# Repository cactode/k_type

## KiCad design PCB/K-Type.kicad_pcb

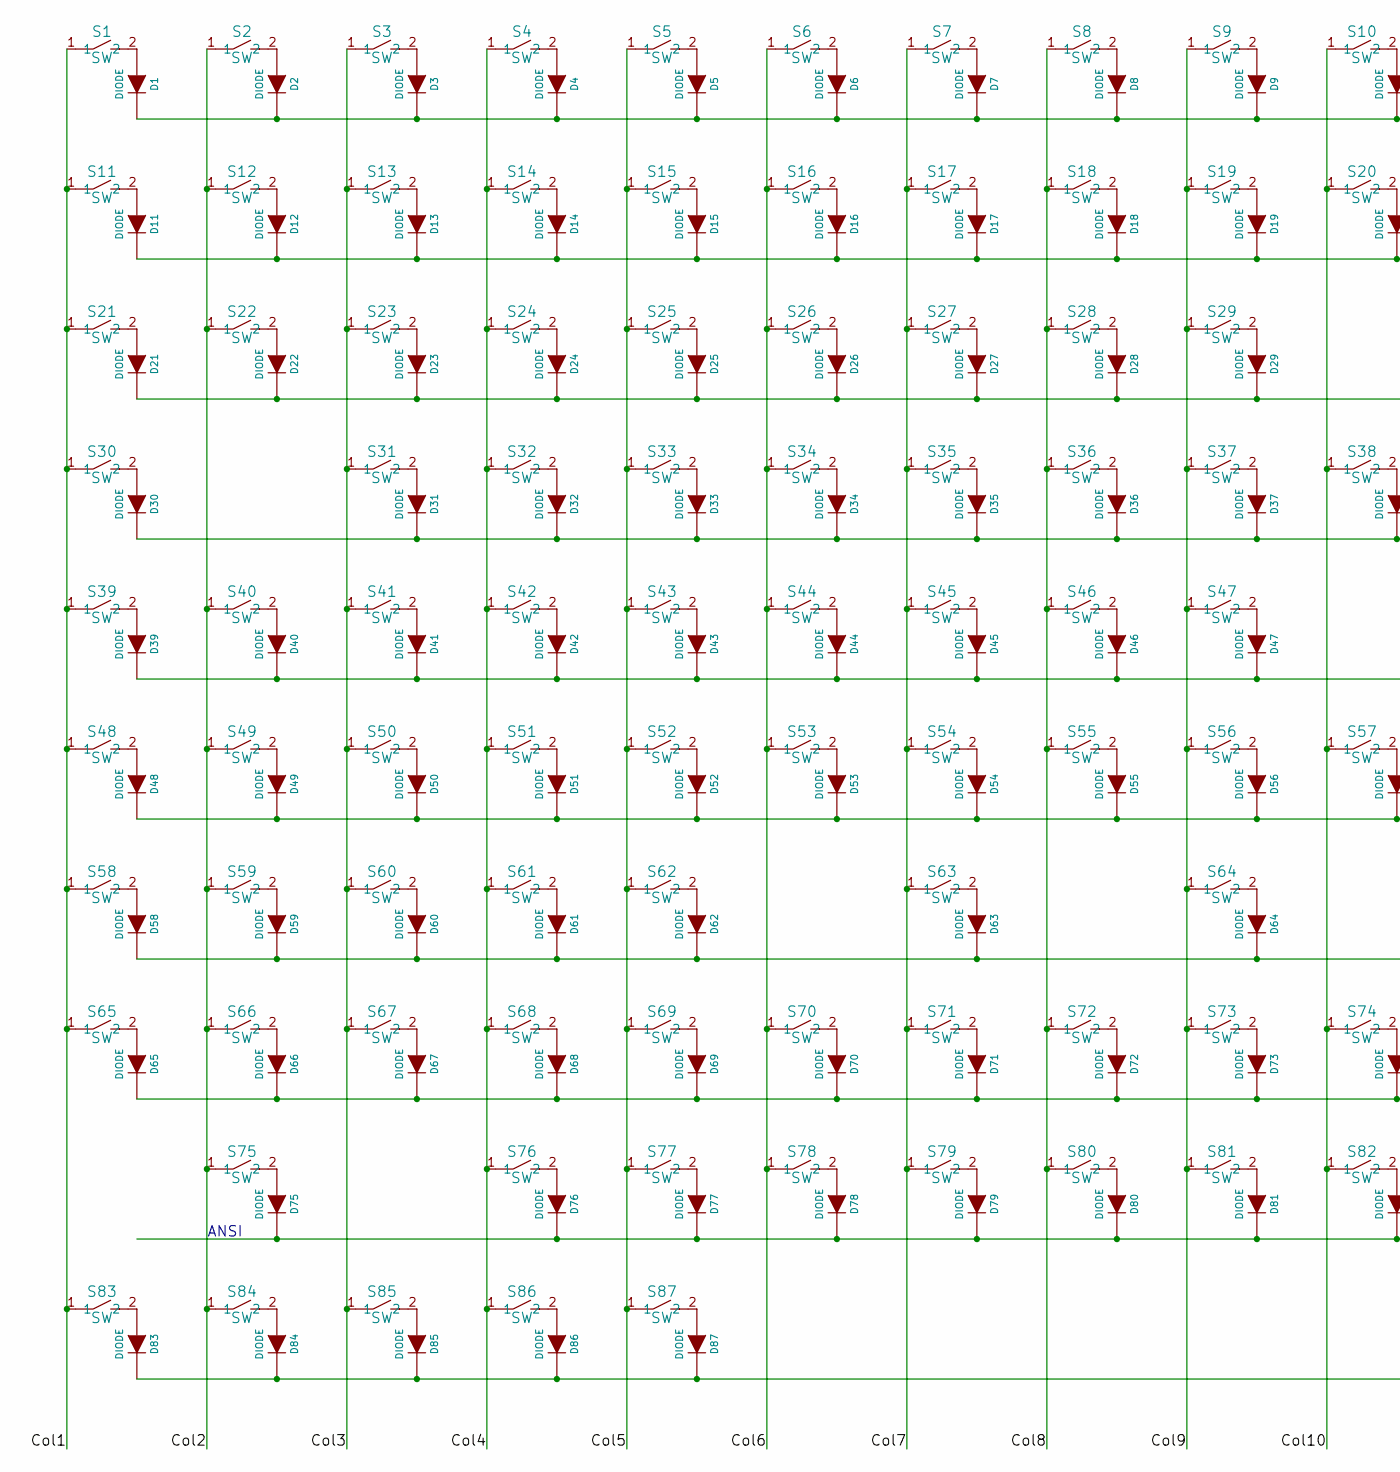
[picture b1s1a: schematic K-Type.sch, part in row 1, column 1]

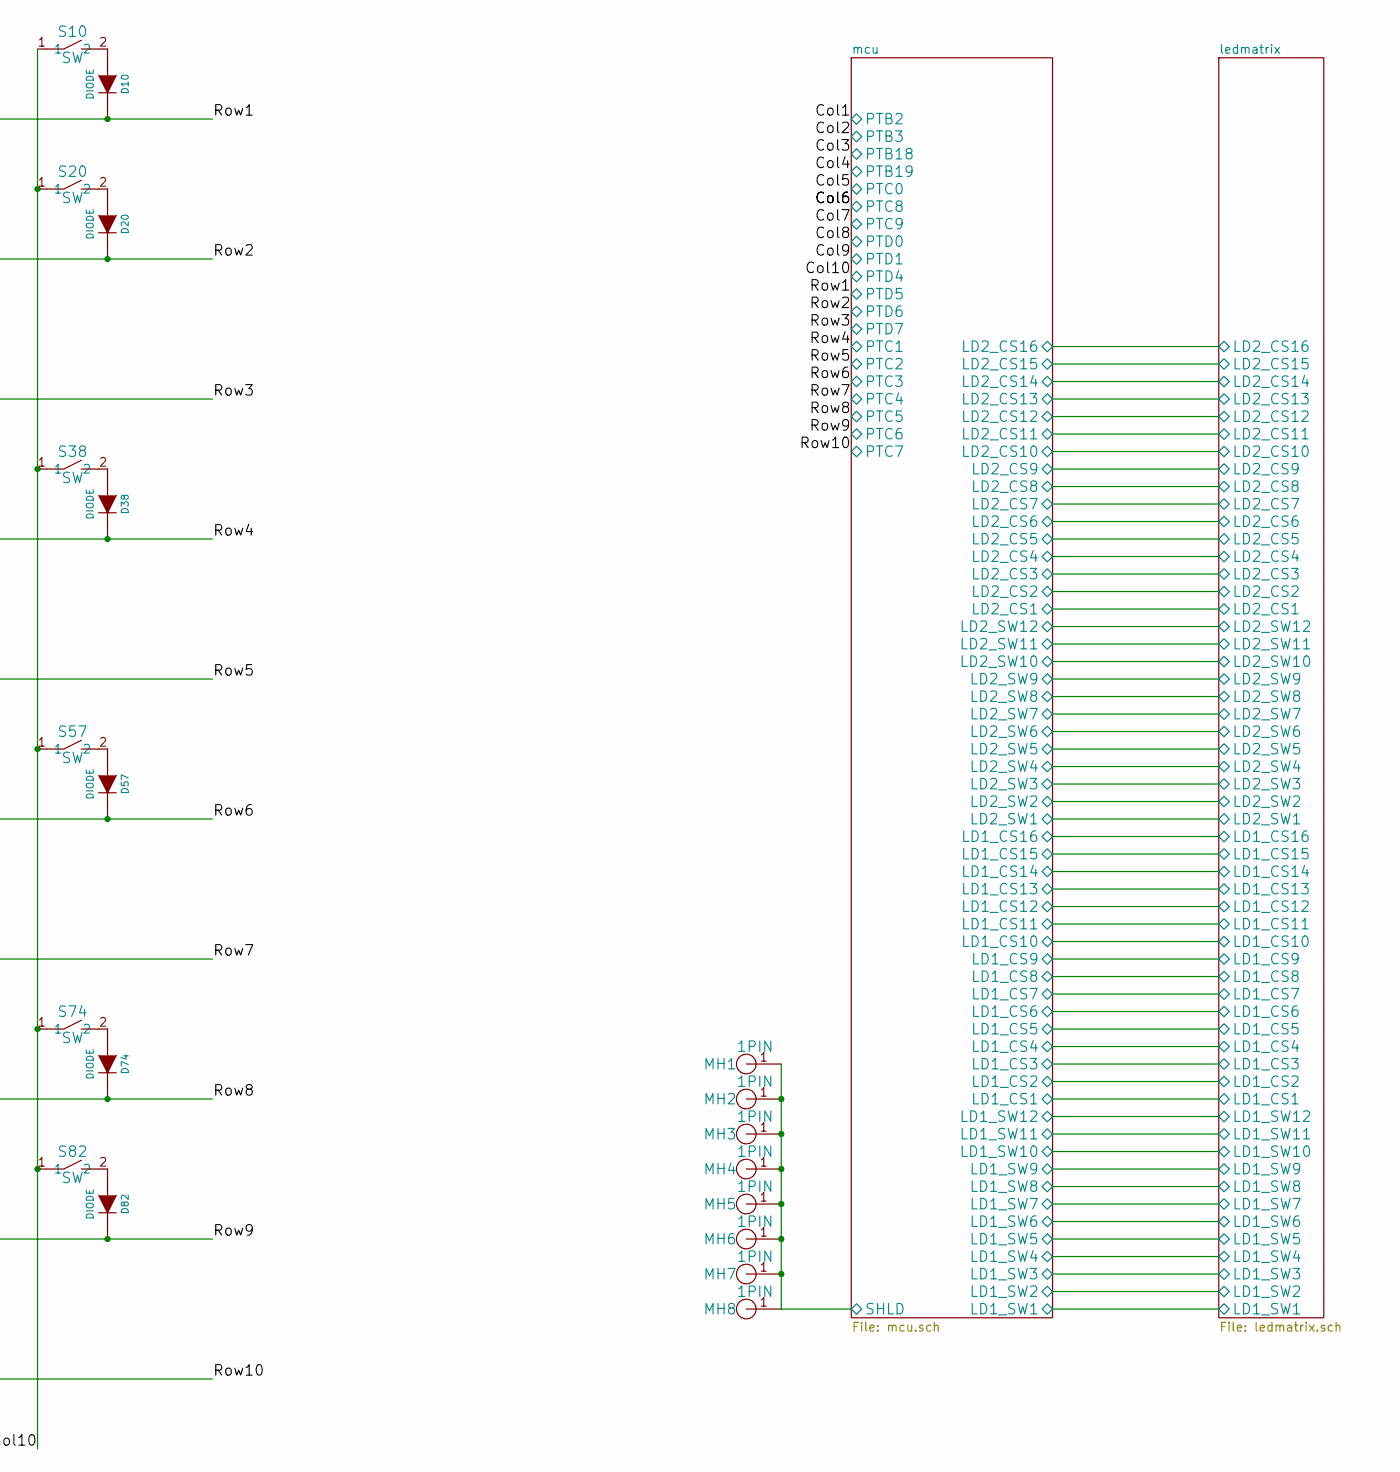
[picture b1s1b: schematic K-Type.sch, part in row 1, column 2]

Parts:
D1, D2, D3, D4, D5, D6, D7, D8, D9, D10, D11, D12, D13, D14, D15, D16, D17, D18, D19, D20, D21, D22, D23, D24, D25, D26, D27, D28, D29, D30, D31, D32, D33, D34, D35, D36, D37, D38, D39, D40, D41, D42, D43, D44, D45, D46, D47, D48, D49, D50, D51, D52, D53, D54, D55, D56, D57, D58, D59, D60, D61, D62, D63, D64, D65, D66, D67, D68, D69, D70, D71, D72, D73, D74, D75, D76, D77, D78, D79, D80, D81, D82, D83, D84, D85, D86, D87: DIODE; SOD-523
MH1, MH2, MH3, MH4, MH5, MH6, MH7, MH8: 1PIN; 1PAD
S1, S2, S3, S4, S5, S6, S7, S8, S9, S10, S11, S12, S13, S14, S15, S16, S17, S18, S19, S20, S21, S22, S23, S24, S25, S26, S27, S28, S29, S30, S31, S32, S33, S34, S35, S36, S37, S38, S39, S40, S41, S42, S43, S44, S45, S46, S47, S48, S49, S50, S51, S52, S53, S54, S55, S56, S57, S58, S59, S60, S61, S62, S63, S64, S65, S66, S67, S68, S69, S70, S71, S72, S73, S74, S75, S76, S77, S78, S79, S80, S81, S82, S83, S84, S85, S86, S87: SW; SW_SOCKET_COMBINED_T

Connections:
/Col1: S1.1, S11.1, S21.1, S30.1, S39.1, S48.1, S58.1, S65.1, S83.1; also elsewhere on the board
/Col2: S2.1, S12.1, S22.1, S40.1, S49.1, S59.1, S66.1, S75.1, S84.1; also elsewhere on the board
/Col3: S3.1, S13.1, S23.1, S31.1, S41.1, S50.1, S60.1, S67.1, S85.1; also elsewhere on the board
/Col4: S4.1, S14.1, S24.1, S32.1, S42.1, S51.1, S61.1, S68.1, S76.1, S86.1; also elsewhere on the board
/Col5: S5.1, S15.1, S25.1, S33.1, S43.1, S52.1, S62.1, S69.1, S77.1, S87.1; also elsewhere on the board
/Col6: S6.1, S16.1, S26.1, S34.1, S44.1, S53.1, S70.1, S78.1; also elsewhere on the board
/Col7: S7.1, S17.1, S27.1, S35.1, S45.1, S54.1, S63.1, S71.1, S79.1; also elsewhere on the board
/Col8: S8.1, S18.1, S28.1, S36.1, S46.1, S55.1, S72.1, S80.1; also elsewhere on the board
/Col9: S9.1, S19.1, S29.1, S37.1, S47.1, S56.1, S64.1, S73.1, S81.1; also elsewhere on the board
/Col10: S10.1, S20.1, S38.1, S57.1, S74.1, S82.1; also elsewhere on the board
/Row1: D1.2 (K), D2.2 (K), D3.2 (K), D4.2 (K), D5.2 (K), D6.2 (K), D7.2 (K), D8.2 (K), D9.2 (K), D10.2 (K); also elsewhere on the board
/Row2: D11.2 (K), D12.2 (K), D13.2 (K), D14.2 (K), D15.2 (K), D16.2 (K), D17.2 (K), D18.2 (K), D19.2 (K), D20.2 (K); also elsewhere on the board
/Row3: D21.2 (K), D22.2 (K), D23.2 (K), D24.2 (K), D25.2 (K), D26.2 (K), D27.2 (K), D28.2 (K), D29.2 (K); also elsewhere on the board
/Row4: D30.2 (K), D31.2 (K), D32.2 (K), D33.2 (K), D34.2 (K), D35.2 (K), D36.2 (K), D37.2 (K), D38.2 (K); also elsewhere on the board
/Row5: D39.2 (K), D40.2 (K), D41.2 (K), D42.2 (K), D43.2 (K), D44.2 (K), D45.2 (K), D46.2 (K), D47.2 (K); also elsewhere on the board
/Row6: D48.2 (K), D49.2 (K), D50.2 (K), D51.2 (K), D52.2 (K), D53.2 (K), D54.2 (K), D55.2 (K), D56.2 (K), D57.2 (K); also elsewhere on the board
/Row7: D58.2 (K), D59.2 (K), D60.2 (K), D61.2 (K), D62.2 (K), D63.2 (K), D64.2 (K); also elsewhere on the board
/Row8: D65.2 (K), D66.2 (K), D67.2 (K), D68.2 (K), D69.2 (K), D70.2 (K), D71.2 (K), D72.2 (K), D73.2 (K), D74.2 (K); also elsewhere on the board
/Row9: D75.2 (K), D76.2 (K), D77.2 (K), D78.2 (K), D79.2 (K), D80.2 (K), D81.2 (K), D82.2 (K); also elsewhere on the board
/Row10: D83.2 (K), D84.2 (K), D85.2 (K), D86.2 (K), D87.2 (K); also elsewhere on the board
/mcu/SHLD: MH1.1, MH2.1, MH3.1, MH4.1, MH5.1, MH6.1, MH7.1, MH8.1; also elsewhere on the board
unnamed: D1.1 (A), S1.2
unnamed: D2.1 (A), S2.2
unnamed: D3.1 (A), S3.2
unnamed: D4.1 (A), S4.2
unnamed: D5.1 (A), S5.2
unnamed: D6.1 (A), S6.2
unnamed: D7.1 (A), S7.2
unnamed: D8.1 (A), S8.2
unnamed: D9.1 (A), S9.2
unnamed: D10.1 (A), S10.2
unnamed: D11.1 (A), S11.2
unnamed: D12.1 (A), S12.2
unnamed: D13.1 (A), S13.2
unnamed: D14.1 (A), S14.2
unnamed: D15.1 (A), S15.2
unnamed: D16.1 (A), S16.2
unnamed: D17.1 (A), S17.2
unnamed: D18.1 (A), S18.2
unnamed: D19.1 (A), S19.2
unnamed: D20.1 (A), S20.2
unnamed: D21.1 (A), S21.2
unnamed: D22.1 (A), S22.2
unnamed: D23.1 (A), S23.2
unnamed: D24.1 (A), S24.2
unnamed: D25.1 (A), S25.2
unnamed: D26.1 (A), S26.2
unnamed: D27.1 (A), S27.2
unnamed: D28.1 (A), S28.2
unnamed: D29.1 (A), S29.2
unnamed: D30.1 (A), S30.2
unnamed: D31.1 (A), S31.2
unnamed: D32.1 (A), S32.2
unnamed: D33.1 (A), S33.2
unnamed: D34.1 (A), S34.2
unnamed: D35.1 (A), S35.2
unnamed: D36.1 (A), S36.2
unnamed: D37.1 (A), S37.2
unnamed: D38.1 (A), S38.2
unnamed: D39.1 (A), S39.2
unnamed: D40.1 (A), S40.2
unnamed: D41.1 (A), S41.2
unnamed: D42.1 (A), S42.2
unnamed: D43.1 (A), S43.2
unnamed: D44.1 (A), S44.2
unnamed: D45.1 (A), S45.2
unnamed: D46.1 (A), S46.2
unnamed: D47.1 (A), S47.2
unnamed: D48.1 (A), S48.2
unnamed: D49.1 (A), S49.2
unnamed: D50.1 (A), S50.2
unnamed: D51.1 (A), S51.2
unnamed: D52.1 (A), S52.2
unnamed: D53.1 (A), S53.2
unnamed: D54.1 (A), S54.2
unnamed: D55.1 (A), S55.2
unnamed: D56.1 (A), S56.2
unnamed: D57.1 (A), S57.2
unnamed: D58.1 (A), S58.2
unnamed: D59.1 (A), S59.2
unnamed: D60.1 (A), S60.2
unnamed: D61.1 (A), S61.2
unnamed: D62.1 (A), S62.2
unnamed: D63.1 (A), S63.2
unnamed: D64.1 (A), S64.2
unnamed: D65.1 (A), S65.2
unnamed: D66.1 (A), S66.2
unnamed: D67.1 (A), S67.2
unnamed: D68.1 (A), S68.2
unnamed: D69.1 (A), S69.2
unnamed: D70.1 (A), S70.2
unnamed: D71.1 (A), S71.2
unnamed: D72.1 (A), S72.2
unnamed: D73.1 (A), S73.2
unnamed: D74.1 (A), S74.2
unnamed: D75.1 (A), S75.2
unnamed: D76.1 (A), S76.2
unnamed: D77.1 (A), S77.2
unnamed: D78.1 (A), S78.2
unnamed: D79.1 (A), S79.2
unnamed: D80.1 (A), S80.2
unnamed: D81.1 (A), S81.2
unnamed: D82.1 (A), S82.2
unnamed: D83.1 (A), S83.2
unnamed: D84.1 (A), S84.2
unnamed: D85.1 (A), S85.2
unnamed: D86.1 (A), S86.2
unnamed: D87.1 (A), S87.2

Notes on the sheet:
ANSI

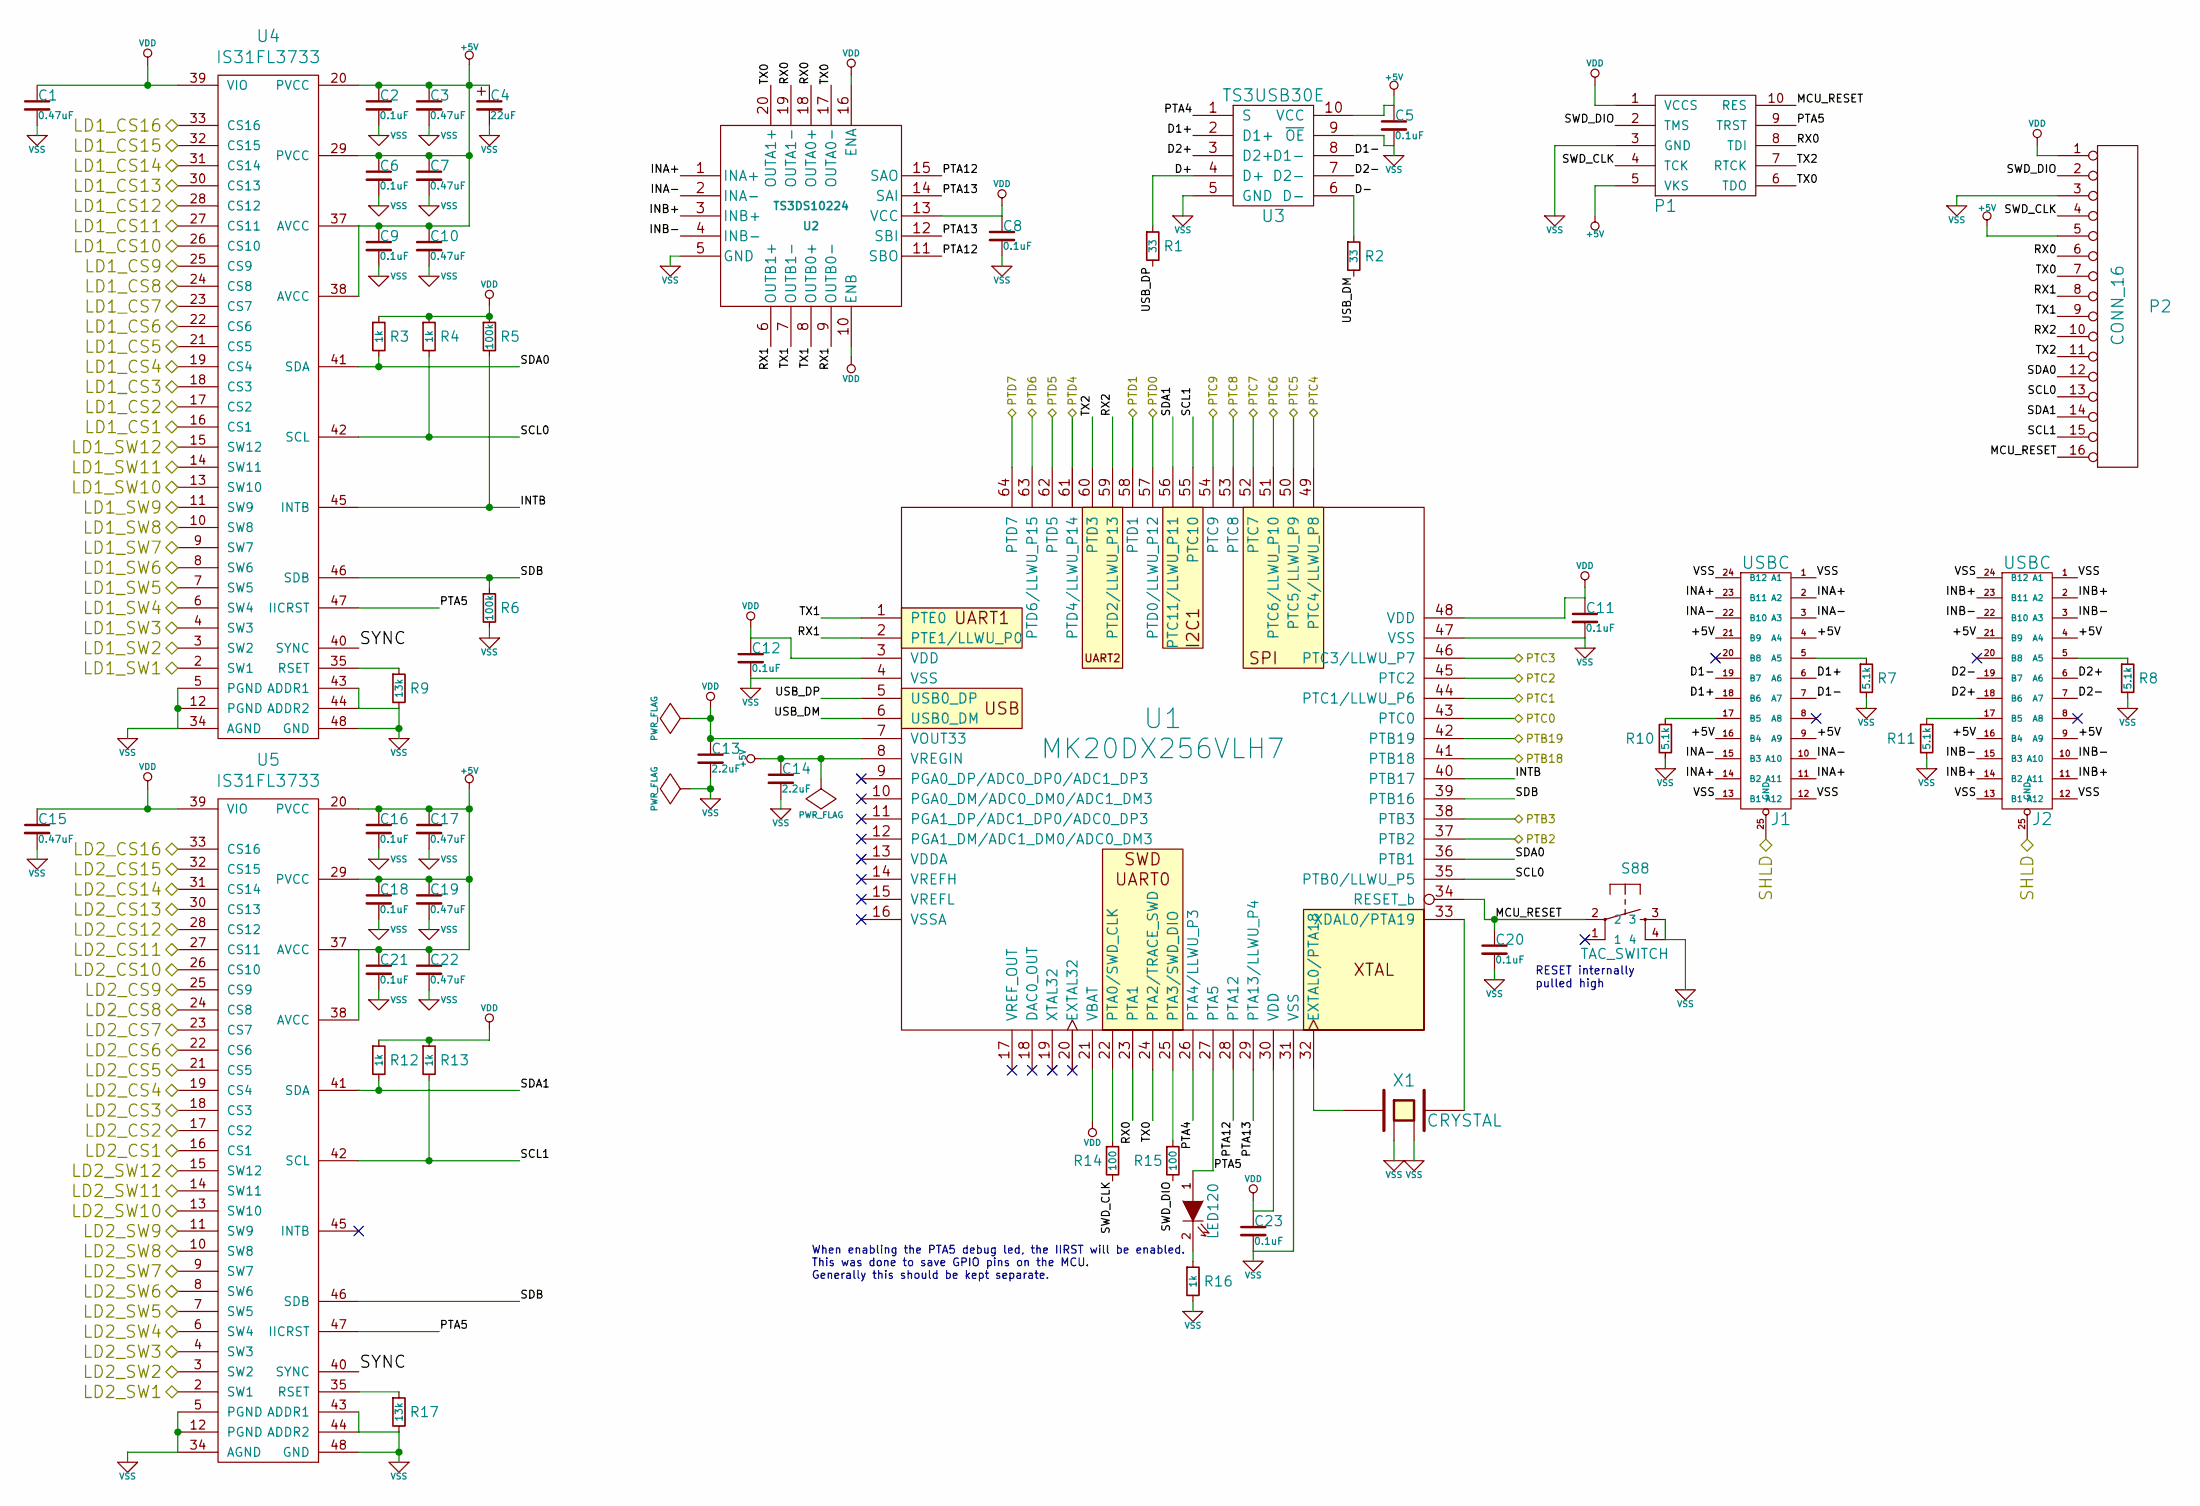
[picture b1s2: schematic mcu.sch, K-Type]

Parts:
C1, C3, C7, C10, C15, C17, C19, C22: 0.47uF; SMD-0402
C2, C5, C6, C8, C9, C11, C12, C16, C18, C20, C21, C23: 0.1uF; SMD-0402
C4: 22uF; SMD-7343-Pol
C13, C14: 2.2uF; SMD-0402
J1, J2: USBC; USB_C_MIDMOUNT_TH_IMPCUT
LED120: LED; LED-0603
P1: FLASH_HDR; JLINK_NEEDLE
P2: CONN_16; HEADER_1x16
R1, R2: 33; SMD-0402
R3, R4, R12, R13, R16: 1k; SMD-0402
R5, R6: 100k; SMD-0402
R7, R8, R10, R11: 5.1k; SMD-0402
R9, R17: 13k; SMD-0402
R14, R15: 100; SMD-0402
S88: TAC_SWITCH; TACT_5.2x5.2
U1: MK20DX256VLH7; LQFP64
U2: TS3DS10224; QFN_20_0.4
U3: TS3USB30E; VSSOP-10
U4, U5: IS31FL3733; QFN-48-6mm-vias
X1: CRYSTAL; NX3225SA

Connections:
+5V: C2.1, C3.1, C4.1, C5.1, C6.1, C7.1, C9.1, C10.1, C14.1, C16.1, C17.1, C18.1, C19.1, C21.1, C22.1, J1.4 (A4), J1.9 (A9), J1.16 (B4), J1.21 (B9), J2.4 (A4), J2.9 (A9), J2.16 (B4), J2.21 (B9), P1.5 (VKS), P2.5, U1.8 (VREGIN), U3.10 (VCC), U4.20 (PVCC), U4.29 (PVCC), U4.37 (AVCC), U4.38 (AVCC), U5.20 (PVCC), U5.29 (PVCC), U5.37 (AVCC), U5.38 (AVCC)
/Col1: U1.37 (PTB2); also elsewhere on the board
/Col2: U1.38 (PTB3); also elsewhere on the board
/Col3: U1.41 (PTB18); also elsewhere on the board
/Col4: U1.42 (PTB19); also elsewhere on the board
/Col5: U1.43 (PTC0); also elsewhere on the board
/Col6: U1.53 (PTC8); also elsewhere on the board
/Col7: U1.54 (PTC9); also elsewhere on the board
/Col8: U1.57 (PTD0/LLWU_P12); also elsewhere on the board
/Col9: U1.58 (PTD1); also elsewhere on the board
/Col10: U1.61 (PTD4/LLWU_P14); also elsewhere on the board
/Row1: U1.62 (PTD5); also elsewhere on the board
/Row2: U1.63 (PTD6/LLWU_P15); also elsewhere on the board
/Row3: U1.64 (PTD7); also elsewhere on the board
/Row4: U1.44 (PTC1/LLWU_P6); also elsewhere on the board
/Row5: U1.45 (PTC2); also elsewhere on the board
/Row6: U1.46 (PTC3/LLWU_P7); also elsewhere on the board
/Row7: U1.49 (PTC4/LLWU_P8); also elsewhere on the board
/Row8: U1.50 (PTC5/LLWU_P9); also elsewhere on the board
/Row9: U1.51 (PTC6/LLWU_P10); also elsewhere on the board
/Row10: U1.52 (PTC7); also elsewhere on the board
/ledmatrix/LD1_CS1: U4.16 (CS1); also elsewhere on the board
/ledmatrix/LD1_CS2: U4.17 (CS2); also elsewhere on the board
/ledmatrix/LD1_CS3: U4.18 (CS3); also elsewhere on the board
/ledmatrix/LD1_CS4: U4.19 (CS4); also elsewhere on the board
/ledmatrix/LD1_CS5: U4.21 (CS5); also elsewhere on the board
/ledmatrix/LD1_CS6: U4.22 (CS6); also elsewhere on the board
/ledmatrix/LD1_CS7: U4.23 (CS7); also elsewhere on the board
/ledmatrix/LD1_CS8: U4.24 (CS8); also elsewhere on the board
/ledmatrix/LD1_CS9: U4.25 (CS9); also elsewhere on the board
/ledmatrix/LD1_CS10: U4.26 (CS10); also elsewhere on the board
/ledmatrix/LD1_CS11: U4.27 (CS11); also elsewhere on the board
/ledmatrix/LD1_CS12: U4.28 (CS12); also elsewhere on the board
/ledmatrix/LD1_CS13: U4.30 (CS13); also elsewhere on the board
/ledmatrix/LD1_CS14: U4.31 (CS14); also elsewhere on the board
/ledmatrix/LD1_CS15: U4.32 (CS15); also elsewhere on the board
/ledmatrix/LD1_CS16: U4.33 (CS16); also elsewhere on the board
/ledmatrix/LD1_SW1: U4.2 (SW1); also elsewhere on the board
/ledmatrix/LD1_SW2: U4.3 (SW2); also elsewhere on the board
/ledmatrix/LD1_SW3: U4.4 (SW3); also elsewhere on the board
/ledmatrix/LD1_SW4: U4.6 (SW4); also elsewhere on the board
/ledmatrix/LD1_SW5: U4.7 (SW5); also elsewhere on the board
/ledmatrix/LD1_SW6: U4.8 (SW6); also elsewhere on the board
/ledmatrix/LD1_SW7: U4.9 (SW7); also elsewhere on the board
/ledmatrix/LD1_SW8: U4.10 (SW8); also elsewhere on the board
/ledmatrix/LD1_SW9: U4.11 (SW9); also elsewhere on the board
/ledmatrix/LD1_SW10: U4.13 (SW10); also elsewhere on the board
/ledmatrix/LD1_SW11: U4.14 (SW11); also elsewhere on the board
/ledmatrix/LD1_SW12: U4.15 (SW12); also elsewhere on the board
/ledmatrix/LD2_CS1: U5.16 (CS1); also elsewhere on the board
/ledmatrix/LD2_CS2: U5.17 (CS2); also elsewhere on the board
/ledmatrix/LD2_CS3: U5.18 (CS3); also elsewhere on the board
/ledmatrix/LD2_CS4: U5.19 (CS4); also elsewhere on the board
/ledmatrix/LD2_CS5: U5.21 (CS5); also elsewhere on the board
/ledmatrix/LD2_CS6: U5.22 (CS6); also elsewhere on the board
/ledmatrix/LD2_CS7: U5.23 (CS7); also elsewhere on the board
/ledmatrix/LD2_CS8: U5.24 (CS8); also elsewhere on the board
/ledmatrix/LD2_CS9: U5.25 (CS9); also elsewhere on the board
/ledmatrix/LD2_CS10: U5.26 (CS10); also elsewhere on the board
/ledmatrix/LD2_CS11: U5.27 (CS11); also elsewhere on the board
/ledmatrix/LD2_CS12: U5.28 (CS12); also elsewhere on the board
/ledmatrix/LD2_CS13: U5.30 (CS13); also elsewhere on the board
/ledmatrix/LD2_CS14: U5.31 (CS14); also elsewhere on the board
/ledmatrix/LD2_CS15: U5.32 (CS15); also elsewhere on the board
/ledmatrix/LD2_CS16: U5.33 (CS16); also elsewhere on the board
/ledmatrix/LD2_SW1: U5.2 (SW1); also elsewhere on the board
/ledmatrix/LD2_SW2: U5.3 (SW2); also elsewhere on the board
/ledmatrix/LD2_SW3: U5.4 (SW3); also elsewhere on the board
/ledmatrix/LD2_SW4: U5.6 (SW4); also elsewhere on the board
/ledmatrix/LD2_SW5: U5.7 (SW5); also elsewhere on the board
/ledmatrix/LD2_SW6: U5.8 (SW6); also elsewhere on the board
/ledmatrix/LD2_SW7: U5.9 (SW7); also elsewhere on the board
/ledmatrix/LD2_SW8: U5.10 (SW8); also elsewhere on the board
/ledmatrix/LD2_SW9: U5.11 (SW9); also elsewhere on the board
/ledmatrix/LD2_SW10: U5.13 (SW10); also elsewhere on the board
/ledmatrix/LD2_SW11: U5.14 (SW11); also elsewhere on the board
/ledmatrix/LD2_SW12: U5.15 (SW12); also elsewhere on the board
/mcu/D1+: J1.6 (A6), J1.18 (B6), U3.2 (D1+)
/mcu/D1-: J1.7 (A7), J1.19 (B7), U3.8 (D1-)
/mcu/D2+: J2.6 (A6), J2.18 (B6), U3.3 (D2+)
/mcu/D2-: J2.7 (A7), J2.19 (B7), U3.7 (D2-)
/mcu/D+: R1.1, U3.4 (D+)
/mcu/D-: R2.1, U3.6 (D-)
/mcu/INA+: J1.2 (A2), J1.11 (A11), J1.14 (B2), J1.23 (B11), U2.1 (INA+)
/mcu/INA-: J1.3 (A3), J1.10 (A10), J1.15 (B3), J1.22 (B10), U2.2 (INA-)
/mcu/INB+: J2.2 (A2), J2.11 (A11), J2.14 (B2), J2.23 (B11), U2.3 (INB+)
/mcu/INB-: J2.3 (A3), J2.10 (A10), J2.15 (B3), J2.22 (B10), U2.4 (INB-)
/mcu/INTB: R5.2, U1.40 (PTB17), U4.45 (INTB)
/mcu/MCU_RESET: C20.1, P1.10 (RES), P2.16, S88.2, U1.34 (RESET_b)
/mcu/PTA4: U1.26 (PTA4/LLWU_P3), U3.1 (S)
/mcu/PTA5: LED120.1 (A), P1.9 (TRST), U1.27 (PTA5), U4.47 (IICRST), U5.47 (IICRST)
/mcu/PTA12: U1.28 (PTA12), U2.11 (SBO), U2.15 (SAO)
/mcu/PTA13: U1.29 (PTA13/LLWU_P4), U2.12 (SBI), U2.14 (SAI)
/mcu/RX0: P1.8 (TDI), P2.6, U1.23 (PTA1), U2.18 (OUTA0+), U2.19 (OUTA1-)
/mcu/RX1: P2.8, U1.2 (PTE1/LLWU_P0), U2.6 (OUTB1+), U2.9 (OUTB0-)
/mcu/RX2: P2.10, U1.59 (PTD2/LLWU_P13)
/mcu/SCL0: P2.13, R4.2, U1.35 (PTB0/LLWU_P5), U4.42 (SCL)
/mcu/SCL1: P2.15, R13.2, U1.55 (PTC10), U5.42 (SCL)
/mcu/SDA0: P2.12, R3.2, U1.36 (PTB1), U4.41 (SDA)
/mcu/SDA1: P2.14, R12.2, U1.56 (PTC11/LLWU_P11), U5.41 (SDA)
/mcu/SDB: R6.1, U1.39 (PTB16), U4.46 (SDB), U5.46 (SDB)
/mcu/SHLD: J1.25 (GND), J2.25 (GND); also elsewhere on the board
/mcu/SWD_CLK: P1.4 (TCK), P2.4, R14.2
/mcu/SWD_DIO: P1.2 (TMS), P2.2, R15.2
/mcu/SYNC: U4.40 (SYNC), U5.40 (SYNC)
/mcu/TX0: P1.6 (TDO), P2.7, U1.24 (PTA2/TRACE_SWD), U2.17 (OUTA0-), U2.20 (OUTA1+)
/mcu/TX1: P2.9, U1.1 (PTE0), U2.7 (OUTB1-), U2.8 (OUTB0+)
/mcu/TX2: P1.7 (RTCK), P2.11, U1.60 (PTD3)
/mcu/USB_DM: R2.2, U1.6 (USB0_DM)
/mcu/USB_DP: R1.2, U1.5 (USB0_DP)
unnamed: J1.5 (A5), R7.1
unnamed: J1.17 (B5), R10.1
unnamed: J2.5 (A5), R8.1
unnamed: J2.17 (B5), R11.1
unnamed: LED120.2 (K), R16.1
unnamed: R9.1, U4.35 (RSET)
unnamed: R14.1, U1.22 (PTA0/SWD_CLK)
unnamed: R15.1, U1.25 (PTA3/SWD_DIO)
unnamed: R17.1, U5.35 (RSET)
unnamed: U1.32 (EXTAL0/PTA18), X1.1
unnamed: U1.33 (XDAL0/PTA19), X1.3
VDD: C1.1, C8.1, C11.1, C12.1, C13.1, C15.1, C23.1, P1.1 (VCCS), P2.1, R3.1, R4.1, R5.1, R12.1, R13.1, U1.3 (VDD), U1.7 (VOUT33), U1.21 (VBAT), U1.30 (VDD), U1.48 (VDD), U2.10 (ENB), U2.13 (VCC), U2.16 (ENA), U4.39 (VIO), U5.39 (VIO)
VSS: C1.2, C2.2, C3.2, C4.2, C5.2, C6.2, C7.2, C8.2, C9.2, C10.2, C11.2, C12.2, C13.2, C14.2, C15.2, C16.2, C17.2, C18.2, C19.2, C20.2, C21.2, C22.2, C23.2, J1.1 (A1), J1.12 (A12), J1.13 (B1), J1.24 (B12), J2.1 (A1), J2.12 (A12), J2.13 (B1), J2.24 (B12), P1.3 (GND), P2.3, R6.2, R7.2, R8.2, R9.2, R10.2, R11.2, R16.2, R17.2, S88.3, S88.4, U1.4 (VSS), U1.31 (VSS), U1.47 (VSS), U2.5 (GND), U3.5 (GND), U3.9 (~OE), U4.5 (PGND), U4.12 (PGND), U4.34 (AGND), U4.43 (ADDR1), U4.44 (ADDR2), U4.48 (GND), U5.5 (PGND), U5.12 (PGND), U5.34 (AGND), U5.43 (ADDR1), U5.44 (ADDR2), U5.48 (GND), X1.2, X1.4

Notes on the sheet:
RESET internally pulled high
When enabling the PTA5 debug led, the IIRST will be enabled. This was done to save GPIO pins on the MCU. Generally this should be kept separate.
